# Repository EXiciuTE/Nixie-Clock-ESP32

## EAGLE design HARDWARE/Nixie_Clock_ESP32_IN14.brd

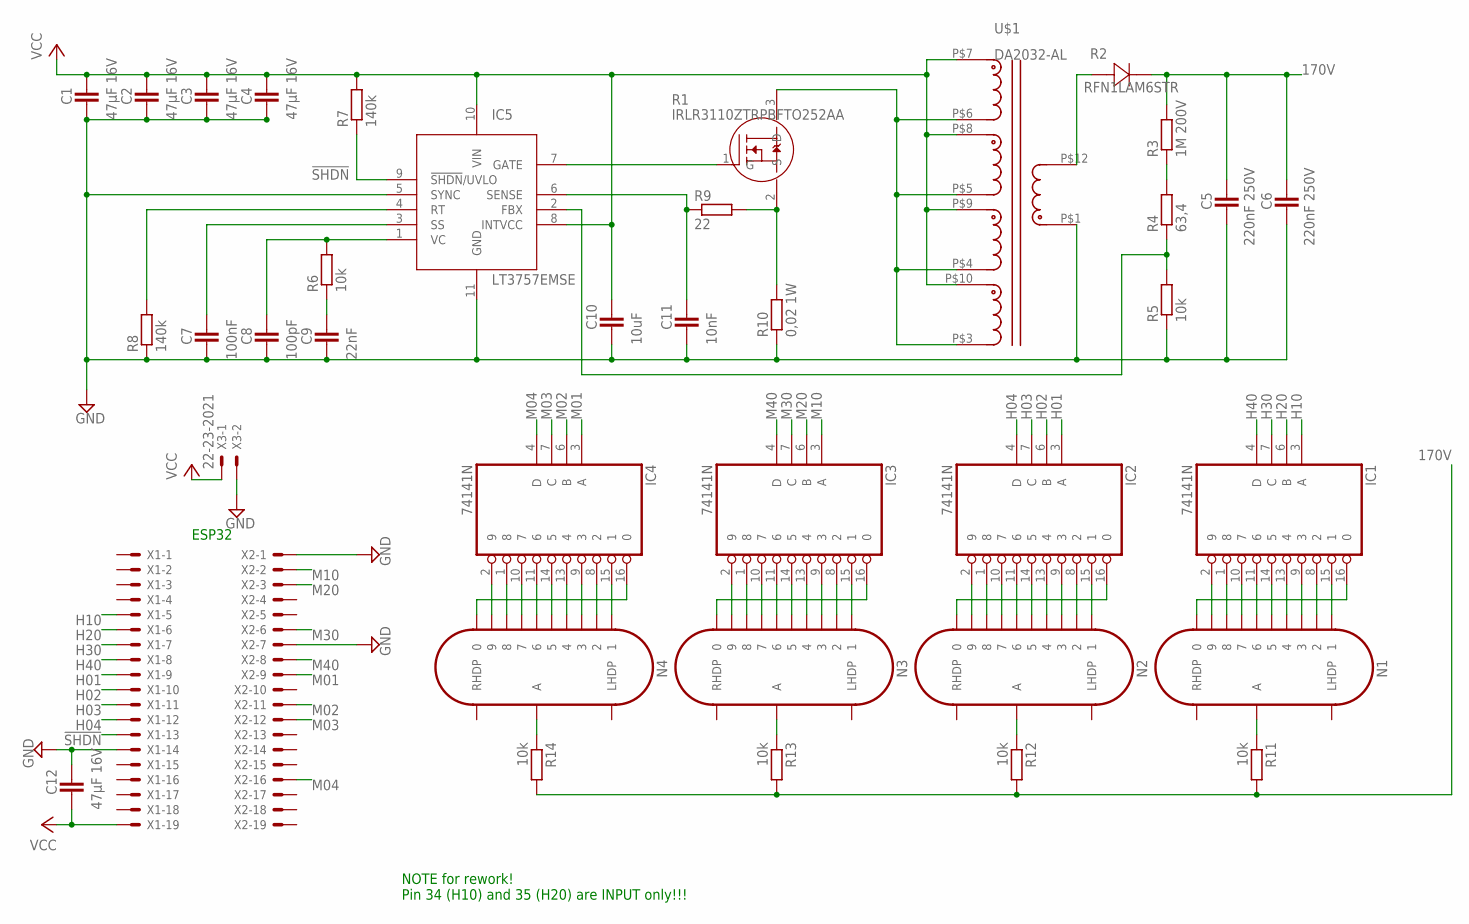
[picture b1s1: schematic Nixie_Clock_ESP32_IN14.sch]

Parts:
C1, C2, C3, C4, C12: 47µF 16V; C1210
C5, C6: 220nF 250V; C1206
C7: 100nF; C0805
C8: 100pF; C0805
C9: 22nF; C0805
C10: 10uF; C0805
C11: 10nF; C0805
IC1, IC2, IC3, IC4: 74141N; DIL16
IC5: LT3757EMSE; MSOP10
N1, N2, N3, N4: IN-14
R1: IRLR3110ZTRPBFTO252AA; TO252
R2: RFN1LAM6STR; DIO_RB050LAM_ROM
R3: 1M 200V; R0805
R4: 63,4; R0805
R5, R6, R11, R12, R13, R14: 10k; R0805
R7, R8: 140k; R0805
R9: 22; R1206
R10: 0,02 1W; R2010
U$1: DA2032-AL
X1, X2: C-GRID-19-70543; 70543-19
X3: 22-23-2021

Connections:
170V: C5.1, C6.1, R2.1 (0), R3.2, R11.2, R12.2, R13.2, R14.2
!SHDN: IC5.9 (!SHDN!/UVLO), R7.1, X1.13
GND: C1.2, C2.2, C3.2, C4.2, C5.2, C6.2, C7.2, C8.2, C9.2, C10.2, C11.2, C12.1, IC1.12 (GND), IC2.12 (GND), IC3.12 (GND), IC4.12 (GND), IC5.5 (SYNC), IC5.11 (GND), R5.1, R8.1, R10.1, U$1.P$1 (1), X1.14, X2.1, X2.7, X3.2
H01: IC2.3 (A), X1.9
H02: IC2.6 (B), X1.10
H03: IC2.7 (C), X1.11
H04: IC2.4 (D), X1.12
H10: IC1.3 (A), X1.5
H20: IC1.6 (B), X1.6
H30: IC1.7 (C), X1.7
H40: IC1.4 (D), X1.8
M01: IC4.3 (A), X2.9
M02: IC4.6 (B), X2.11
M03: IC4.7 (C), X2.12
M04: IC4.4 (D), X2.16
M10: IC3.3 (A), X2.2
M20: IC3.6 (B), X2.3
M30: IC3.7 (C), X2.6
M40: IC3.4 (D), X2.8
unnamed: IC1.16 (0), N1.0
unnamed: R1.3 (D), U$1.P$3 (3), U$1.P$4 (4), U$1.P$5 (5), U$1.P$6 (6)
unnamed: IC5.7 (GATE), R1.1 (G)
unnamed: C11.1, IC5.6 (SENSE), R9.1
unnamed: R1.2 (S), R9.2, R10.2
unnamed: C7.1, IC5.3 (SS)
unnamed: C8.1, IC5.1 (VC), R6.2
unnamed: C9.1, R6.1
unnamed: IC5.4 (RT), R8.2
unnamed: R3.1, R4.2
unnamed: R2.2 (1), U$1.P$12 (12)
unnamed: IC1.2 (9), N1.9
unnamed: IC5.2 (FBX), R4.1, R5.2
unnamed: IC1.1 (8), N1.8
unnamed: IC1.10 (7), N1.7
unnamed: IC1.11 (6), N1.6
unnamed: IC1.14 (5), N1.5
unnamed: IC1.13 (4), N1.4
unnamed: IC1.9 (3), N1.3
unnamed: IC1.8 (2), N1.2
unnamed: IC1.15 (1), N1.1
unnamed: IC2.16 (0), N2.0
unnamed: IC2.2 (9), N2.9
unnamed: IC2.1 (8), N2.8
unnamed: IC2.10 (7), N2.7
unnamed: IC2.11 (6), N2.6
unnamed: IC2.14 (5), N2.5
unnamed: IC2.13 (4), N2.4
unnamed: IC2.9 (3), N2.3
unnamed: IC2.8 (2), N2.2
unnamed: IC2.15 (1), N2.1
unnamed: IC3.16 (0), N3.0
unnamed: IC3.2 (9), N3.9
unnamed: IC3.1 (8), N3.8
unnamed: IC3.10 (7), N3.7
unnamed: IC3.11 (6), N3.6
unnamed: IC3.14 (5), N3.5
unnamed: IC3.13 (4), N3.4
unnamed: IC3.9 (3), N3.3
unnamed: IC3.8 (2), N3.2
unnamed: IC3.15 (1), N3.1
unnamed: IC4.16 (0), N4.0
unnamed: IC4.2 (9), N4.9
unnamed: IC4.1 (8), N4.8
unnamed: IC4.10 (7), N4.7
unnamed: IC4.11 (6), N4.6
unnamed: IC4.14 (5), N4.5
unnamed: IC4.13 (4), N4.4
unnamed: IC4.9 (3), N4.3
unnamed: IC4.8 (2), N4.2
unnamed: IC4.15 (1), N4.1
unnamed: N1.A, R11.1
unnamed: N2.A, R12.1
unnamed: N3.A, R13.1
unnamed: N4.A, R14.1
VCC: C1.1, C2.1, C3.1, C4.1, C10.1, C12.2, IC1.5 (VCC), IC2.5 (VCC), IC3.5 (VCC), IC4.5 (VCC), IC5.8 (INTVCC), IC5.10 (VIN), R7.2, U$1.P$7 (7), U$1.P$8 (8), U$1.P$9 (9), U$1.P$10 (10), X1.19, X3.1

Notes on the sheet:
ESP32
NOTE for rework! Pin 34 (H10) and 35 (H20) are INPUT only!!!

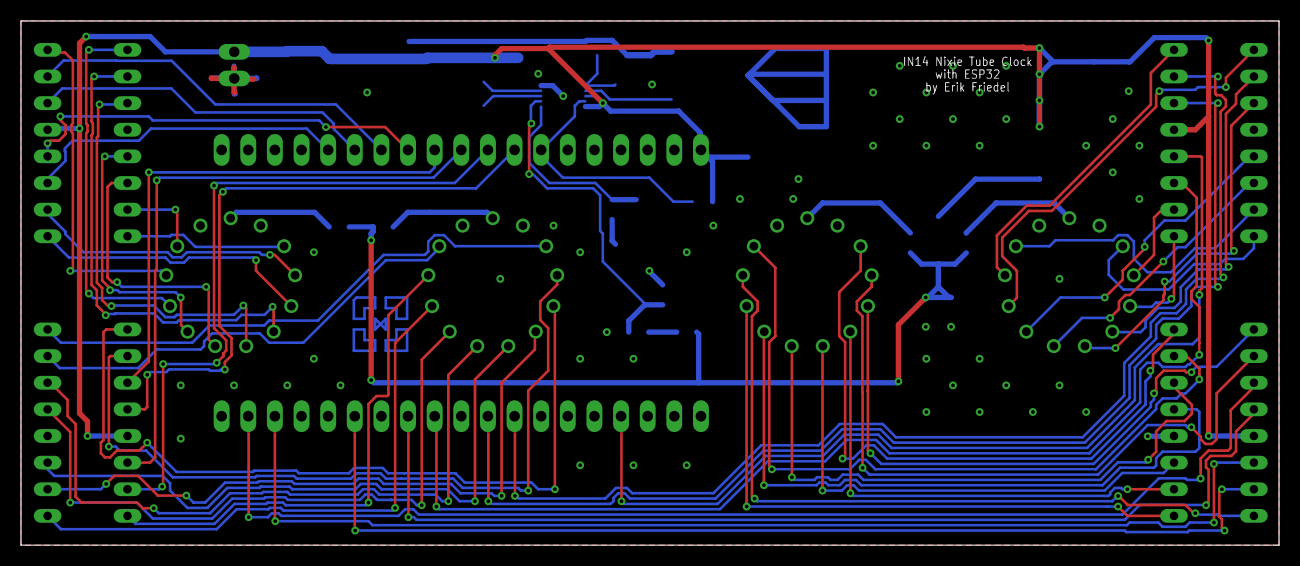
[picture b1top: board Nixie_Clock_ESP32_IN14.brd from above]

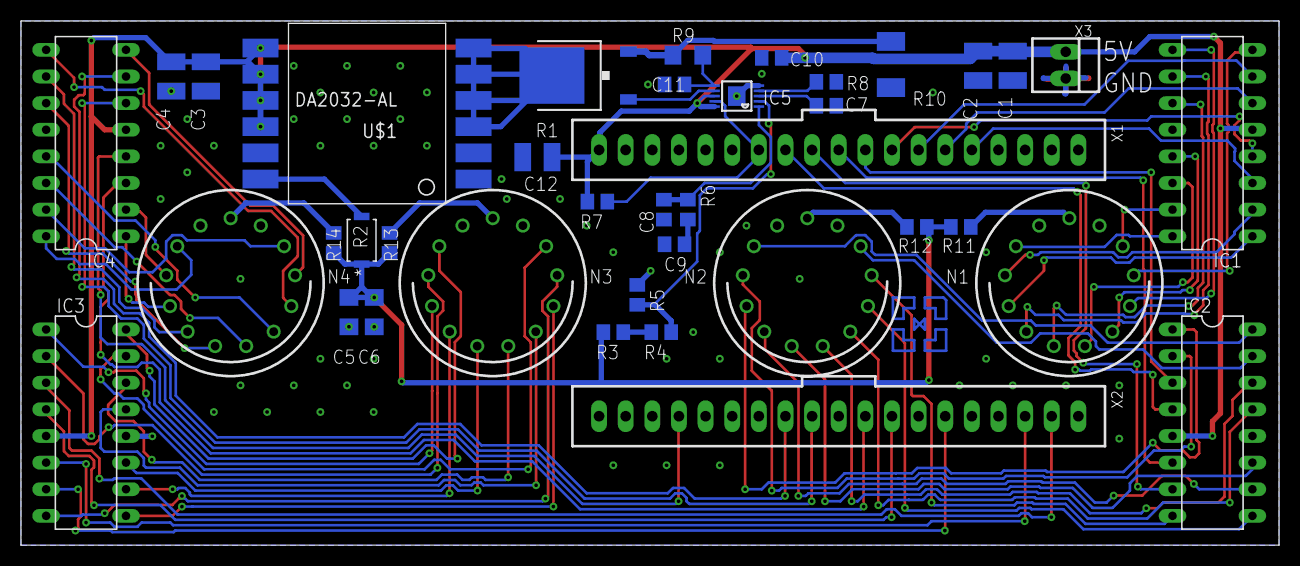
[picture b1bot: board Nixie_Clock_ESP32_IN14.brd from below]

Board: 2 copper layers, 120.0 x 50.0 mm, 39 parts (39 on the bottom side), 75 nets.

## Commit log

2021-03-15 Add files via upload
    initial commit
2025-07-21 rearrange repo, before switching to v1.1

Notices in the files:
parts and their libraries:
COPYRIGHT: Copyright (C) 2018 Accelerated Designs. All rights reserved
